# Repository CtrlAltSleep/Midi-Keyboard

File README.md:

# Midi-Keyboard
this is for Half life week 3 where i learn how to turn circuits into sound by creating a Midi Keyboard. this was made in KICad software and i designed it to be as simple as possible to understand for begginers

here are images people might find necessary to understand

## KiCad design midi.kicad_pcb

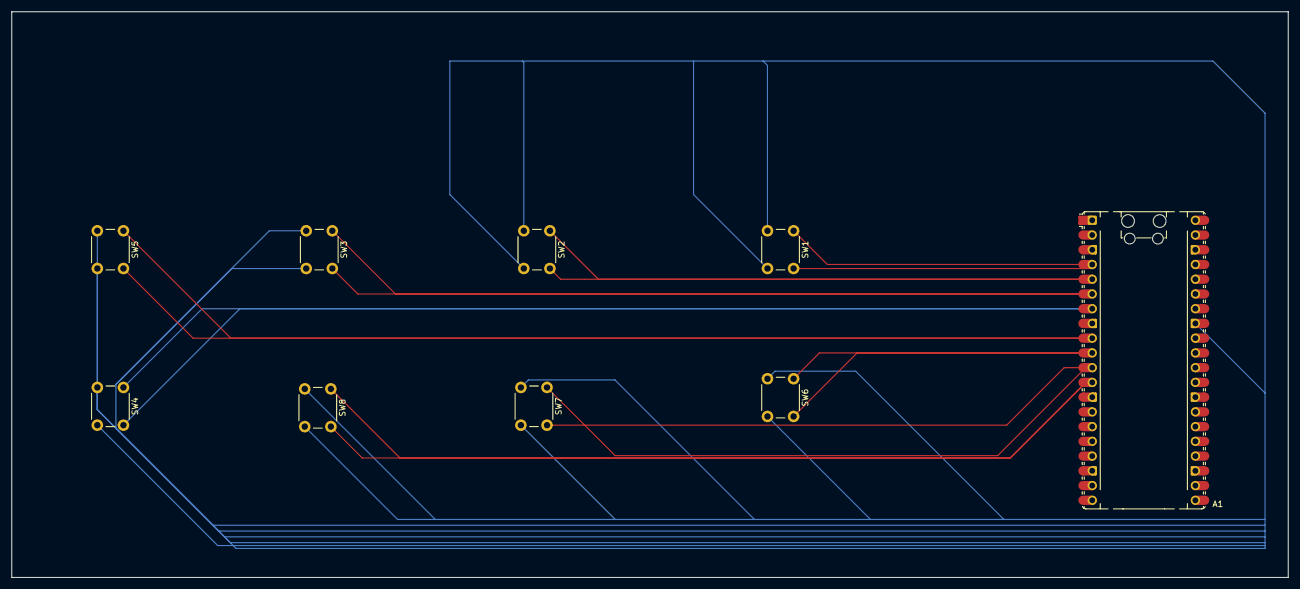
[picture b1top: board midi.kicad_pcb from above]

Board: 2 copper layers, 220.0 x 97.5 mm, 9 parts (0 on the bottom side), 9 nets.

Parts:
A1: RaspberryPi_Pico; RaspberryPi_Pico_Common_Unspecified
SW1, SW2, SW3, SW4, SW5, SW6, SW7, SW8: SW_Push; SW_PUSH_6mm_H4.3mm

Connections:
GND: A1.33 (AGND), SW1.2, SW2.2, SW3.2, SW4.2, SW5.2, SW6.2, SW7.2, SW8.2
unnamed: A1.4 (GPIO2), SW1.1
unnamed: A1.5 (GPIO3), SW2.1
unnamed: A1.6 (GPIO4), SW3.1
unnamed: A1.7 (GPIO5), SW4.1
unnamed: A1.9 (GPIO6), SW5.1
unnamed: A1.10 (GPIO7), SW6.1
unnamed: A1.11 (GPIO8), SW7.1
unnamed: A1.12 (GPIO9), SW8.1
